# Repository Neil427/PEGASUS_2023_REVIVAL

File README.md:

# PEGASUS_2023_REVIVAL
:

NOTE: FROM 2025 ON DEVELOPMENT WILL CONTINUE ON MY DEDICATED VINTAGE COMPUTER GITHUB "NeilsVintageComputers"

:

This is a reproduction of the first computer I owned back in 1981
After many years and house moves I now dont know whatever happened to it, it may have been sold or dumped, I have no idea.

One day while sorting through floppy disk backups I found all the Pegasus eprom files I had saved dated 1988, including some extra monitor eproms I had made that I think one was for Baudot printer output and the other was for a modification I had made fitting a 6845 CRT controller.
The discovery of the Eprom files and manual with schematics gave me the idea of building a replica, I mentioned this to a mate Gavin who told me he had a unused blank Pegasus circuit board that I could have and build up.  I decided not to build up the board as a bare board is probably quite rare, and without components on it was a great help in verifying the original schematic and designing this new pcb.

Searching found a huge repository on github of Aamber Pegasus software and information (github/Neoncluster/Aamber-Pegasus-remake), the information is a great recource and thanks to Neoncluster for preserving it. 

It looked like this remake was not completed so I decided to start from scratch from the original Pegasus schematics.
I drew the original schematics from the Pegasus manual into Kicad (thanks to Neoncluster for your Kicad Library), finding a few errors in the original documentation which I could verify on the blank PCB. Then started a new Kicad project for the new PCB, I added in the video jitter mods that were done to correct problems with the original Pegasus video design one of which was designed by Gavin back in the 80s.   NOTE: These jitter mds require the use of MON23a monitor eprom.

I have added a 16K Eprom to the board so as to be able to have the three Xbasic eproms on board without needing an expansion board like I used back in 1981, there is also a switch to select two halves of a 32K eprom giving the equivalent of 8 original 4K eproms. 
Also added are option jumpers for the three TMS2532 eprom sockets to allow selection of either TMS2532 or TMS2732 eproms as the TMS2532 is not easy to find these days, and a LED for tape data indication. 

All ICs used are the original ones as in the original pegasus bom, the 74LS logic chips are still available and most of the rareish chips were available on Ebay and other places. The only expensive (read very rare) one was the MCM66710 character generator which I found on Ebay only.

Amazingly it worked first time! All the hours of tracing out what I thought were errors in the original schematic had paid off. 
There was one minor problem I found, if you have no memory/eprom expansion board plugged in but have the LS245 buffer fitted the firmware can read in random data from the expansion bus when doing its check of RamEnd. This causes Basic (or any other program using RamEnd) to crash when trying to use non-existing memory. By luck after trying a few brands (inclding 74HCT245s) I discovered that a Ti brand SN74LS245N worked (Maybe that brand was used in the original Pegasus as I dont remember this being a problem back in 1981), the memory check now doesnt find non-existant memory on the expansion bus. Some pullup resistors on the expansion bus side of these buffers would be a good idea.

Now I had a working Pegasus all I needed was a keyboard. The manual doesnt have the keyboard schematic so this was a lot of work systematically producing key closures and seeing what character they produced!  The first pcb mostly worked, a few of the non printing keys were wrong, so it took another board to correct these. I havent found any errors yet with the current board.  You cant buy cheap Chinese keycaps exactly the same as the old Pegasus keyboard so I have found a set with logical alternatives (i.e."END" for the Break key etc.), you could of course print some stickers with the correct name.
The keyboard has a 34-pin IDC connector as I am going to use it with another board I am working on. For use on the Pegasus main board the "even" side of the idc connector (pins 2-----32) plug into the SIL connector on the main board, alternatively a 16-pin SIL header can be inserted in keyboard pcb connector positions 2-----32 to allow use of SIL connectors as in the original Pegasus (Though my sketchy memory is telling me the KB end of the cable might have been soldered direct to the pcb).  
There are two unused LEDs on the Keyboard pcb intended for use as Power On and Cassette Data, these appear on the 34-pin connector but are not brought out on the main board.

NOTES/ISSUES:
- The resistor on the rear of the pcb is a pullup on the bit7 input to the video output shift register (not in the original Pegasus design) to try and remove a small video disturbance at the top of the screen before the first video character line when in graphics mode. It definalely helped but there is still a small disturbance. Need to look into this further.
Further investigation found a faulty 6809 driving one or two of the address lines to only about 2.5V
Needs further investigation and maybe a "improved" design board to be produced as it looks like the original Pegasus design has many more than 4 LS-TTL loads, as specified in the 6809 datasheet, on the address and data lines. It did still work ok with six out of seven 6809 chips I tried. Just one didnt work 100% reliably.
- The 127p capacitor C10 on the dotclock oscillator can be adjusted to trim the dotclock frequency. I noticed on my build that the shift register was clocking out a extra bit making the characters wider than they should be, not really noticeable in text mode but in inverse char graphics mode there would be a "lit up" column of dots at the right of each character.  If the dotclock is too slow the oposite will happen which is noticeable in both text and graphics mode as trimming of the right most dot of a character. I ended up with 138pF (120p + 18p).
- The PCB although the same dimension as the original cant be slid into the original Pegasus square white case as I inadvertently laid the power tracks too close to the edge of the pcb!
- The resistor footprint used is a bit large, needs reducing if producing a update to the board.
  
Here are some phtos of the finished "Pegasus"

Neil

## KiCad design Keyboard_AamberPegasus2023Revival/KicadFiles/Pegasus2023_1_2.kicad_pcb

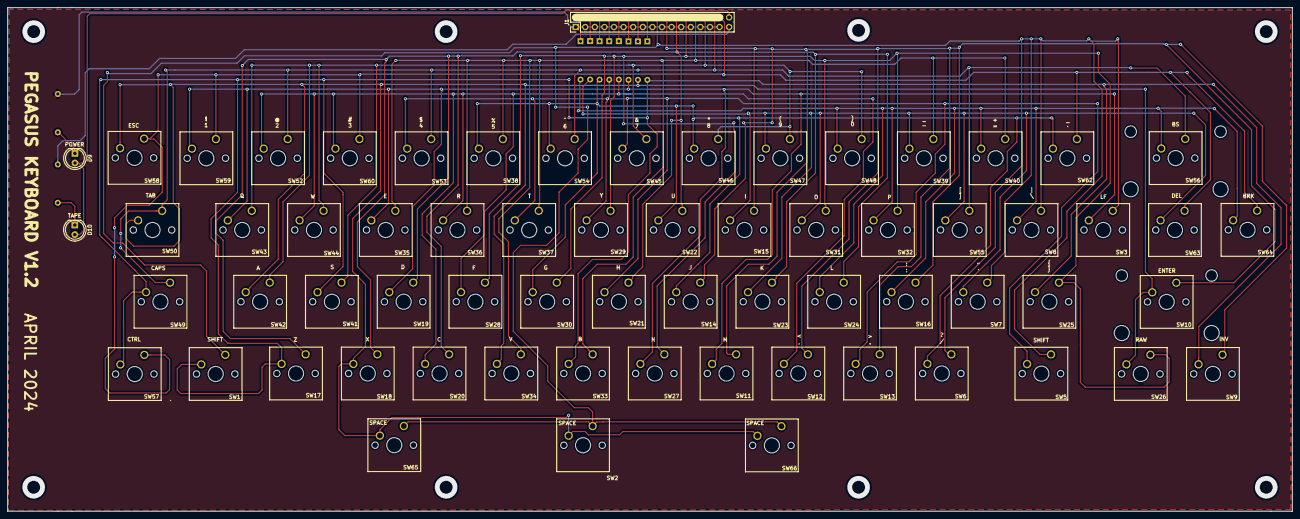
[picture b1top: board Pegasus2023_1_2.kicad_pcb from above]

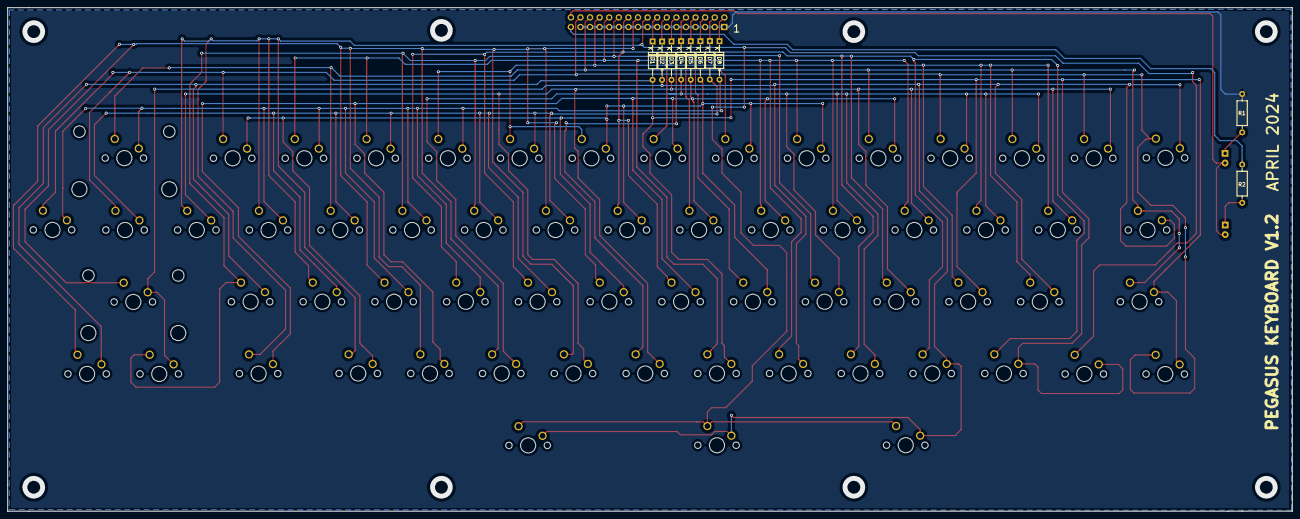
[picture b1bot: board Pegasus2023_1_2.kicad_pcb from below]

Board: 2 copper layers, 340.2 x 133.4 mm, 76 parts (10 on the bottom side), 29 nets.

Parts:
D1, D2, D3, D4, D5, D6, D7, D8: BAT42; D_DO-35_SOD27_P10.16mm_Horizontal
D9: POWER LED; LED_D5.0mm
D10: TAPE LED; LED_D5.0mm
J1: Conn_02x17_Odd_Even; PinHeader_2x17_P2.54mm_Vertical
R1, R2: 470R; R_Axial_DIN0207_L6.3mm_D2.5mm_P10.16mm_Horizontal
SW1: LH SHIFT; SW_Cherry_MX_1.75u_PCB
SW2: SPACE; SW_Cherry_MX_1.00u_PCB
SW3: LF; SW_Cherry_MX_1.00u_PCB
SW5: RH SHIFT; SW_Cherry_MX_1.75u_PCB
SW6: / & ?; SW_Cherry_MX_1.00u_PCB
SW7: ' & "; SW_Cherry_MX_1.00u_PCB
SW8: \ & |; SW_Cherry_MX_1.00u_PCB
SW9: INV; SW_Cherry_MX_1.00u_PCB
SW10: RETURN; SW_Cherry_MX_2.25u_PCB
SW11: M; SW_Cherry_MX_1.00u_PCB
SW12: <; SW_Cherry_MX_1.00u_PCB
SW13: >; SW_Cherry_MX_1.00u_PCB
SW14: J; SW_Cherry_MX_1.00u_PCB
SW15: I; SW_Cherry_MX_1.00u_PCB
SW16: ; & :; SW_Cherry_MX_1.00u_PCB
SW17: Z; SW_Cherry_MX_1.00u_PCB
SW18: X; SW_Cherry_MX_1.00u_PCB
SW19: D; SW_Cherry_MX_1.00u_PCB
SW20: C; SW_Cherry_MX_1.00u_PCB
SW21: H; SW_Cherry_MX_1.00u_PCB
SW22: U; SW_Cherry_MX_1.00u_PCB
SW23: K; SW_Cherry_MX_1.00u_PCB
SW24: L; SW_Cherry_MX_1.00u_PCB
SW25: { & }; SW_Cherry_MX_1.00u_PCB
SW26: RAW; SW_Cherry_MX_1.00u_PCB
SW27: N; SW_Cherry_MX_1.00u_PCB
SW28: F; SW_Cherry_MX_1.00u_PCB
SW29: Y; SW_Cherry_MX_1.00u_PCB
SW30: G; SW_Cherry_MX_1.00u_PCB
SW31: O; SW_Cherry_MX_1.00u_PCB
SW32: P; SW_Cherry_MX_1.00u_PCB
SW33: B; SW_Cherry_MX_1.00u_PCB
SW34: V; SW_Cherry_MX_1.00u_PCB
SW35: E; SW_Cherry_MX_1.00u_PCB
SW36: R; SW_Cherry_MX_1.00u_PCB
SW37: T; SW_Cherry_MX_1.00u_PCB
SW38: 5 & %; SW_Cherry_MX_1.00u_PCB
SW39: - & _; SW_Cherry_MX_1.00u_PCB
SW40: = & +; SW_Cherry_MX_1.00u_PCB
SW41: S; SW_Cherry_MX_1.00u_PCB
SW42: A; SW_Cherry_MX_1.00u_PCB
SW43: Q; SW_Cherry_MX_1.00u_PCB
SW44: W; SW_Cherry_MX_1.00u_PCB
SW45: 7 & &; SW_Cherry_MX_1.00u_PCB
SW46: 8 & *; SW_Cherry_MX_1.00u_PCB
SW47: 9 & (; SW_Cherry_MX_1.00u_PCB
SW48: 0 & ); SW_Cherry_MX_1.00u_PCB
SW49: CAPS; SW_Cherry_MX_1.25u_PCB
SW50: TAB; SW_Cherry_MX_1.50u_PCB
SW52: 2 & @; SW_Cherry_MX_1.00u_PCB
SW53: 4 & $; SW_Cherry_MX_1.00u_PCB
SW54: 6 & ^; SW_Cherry_MX_1.00u_PCB
SW55: ] & [; SW_Cherry_MX_1.00u_PCB
SW56: BS; SW_Cherry_MX_2.00u_PCB
SW57: CTRL; SW_Cherry_MX_1.00u_PCB
SW58: ESC; SW_Cherry_MX_1.00u_PCB
SW59: 1 & !; SW_Cherry_MX_1.00u_PCB
SW60: 3 & #; SW_Cherry_MX_1.00u_PCB
SW62: ~ & `; SW_Cherry_MX_1.00u_PCB
SW63: DEL; SW_Cherry_MX_1.00u_PCB
SW64: BRK; SW_Cherry_MX_1.00u_PCB
SW65: Lspace; SW_Cherry_MX_1.00u_PCB
SW66: Rspace; SW_Cherry_MX_1.00u_PCB

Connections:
7-9: D2.2, SW2.2, SW10.2, SW18.2, SW26.2, SW34.2, SW42.2, SW50.2, SW58.2, SW65.2, SW66.2
+5V: D9.2, D10.2, J1.34
GND: J1.1, J1.3, J1.5, J1.7, J1.9, J1.11, J1.13, J1.15, J1.17, J1.19, J1.21, J1.23, J1.25, J1.27, J1.29, J1.31, R1.1
unnamed: D1.1, J1.16
unnamed: D1.2, SW1.2, SW9.2, SW17.2, SW25.2, SW33.2, SW41.2, SW49.2, SW57.2
unnamed: D2.1, J1.14
unnamed: D3.1, J1.12
unnamed: D3.2, SW3.2, SW11.2, SW19.2, SW27.2, SW35.2, SW43.2, SW59.2
unnamed: D4.1, J1.10
unnamed: D4.2, SW12.2, SW20.2, SW28.2, SW36.2, SW44.2, SW52.2, SW60.2
unnamed: D5.1, J1.8
unnamed: D5.2, SW5.2, SW13.2, SW21.2, SW29.2, SW37.2, SW45.2, SW53.2
unnamed: D6.1, J1.6
unnamed: D6.2, SW6.2, SW14.2, SW22.2, SW30.2, SW38.2, SW46.2, SW54.2, SW62.2
unnamed: D7.1, J1.4
unnamed: D7.2, SW7.2, SW15.2, SW23.2, SW31.2, SW39.2, SW47.2, SW55.2, SW63.2
unnamed: D8.1, J1.2
unnamed: D8.2, SW8.2, SW16.2, SW24.2, SW32.2, SW40.2, SW48.2, SW56.2, SW64.2
unnamed: D9.1, R1.2
unnamed: D10.1, R2.2
unnamed: J1.18, SW1.1, SW2.1, SW3.1, SW5.1, SW6.1, SW7.1, SW8.1, SW65.1, SW66.1
unnamed: J1.20, SW9.1, SW10.1, SW11.1, SW12.1, SW13.1, SW14.1, SW15.1, SW16.1
unnamed: J1.22, SW17.1, SW18.1, SW19.1, SW20.1, SW21.1, SW22.1, SW23.1, SW24.1
unnamed: J1.24, SW25.1, SW26.1, SW27.1, SW28.1, SW29.1, SW30.1, SW31.1, SW32.1
unnamed: J1.26, SW33.1, SW34.1, SW35.1, SW36.1, SW37.1, SW38.1, SW39.1, SW40.1
unnamed: J1.28, SW41.1, SW42.1, SW43.1, SW44.1, SW45.1, SW46.1, SW47.1, SW48.1
unnamed: J1.30, SW49.1, SW50.1, SW52.1, SW53.1, SW54.1, SW55.1, SW56.1
unnamed: J1.32, SW57.1, SW58.1, SW59.1, SW60.1, SW62.1, SW63.1, SW64.1
unnamed: J1.33, R2.1

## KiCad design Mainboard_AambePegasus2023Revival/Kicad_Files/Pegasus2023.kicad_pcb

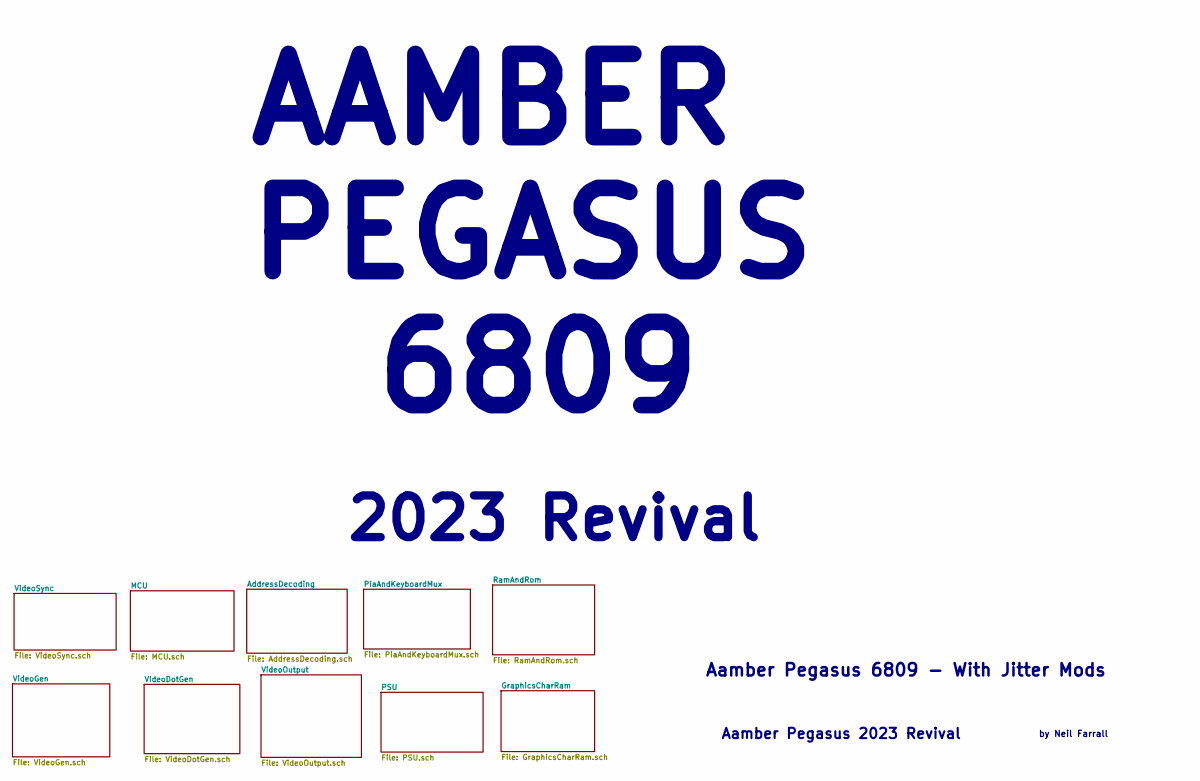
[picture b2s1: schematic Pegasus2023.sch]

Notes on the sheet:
Aamber Pegasus 2023 Revival
by Neil Farrall
Aamber Pegasus 6809 - With Jitter Mods
AAMBER PEGASUS 6809
2023 Revival

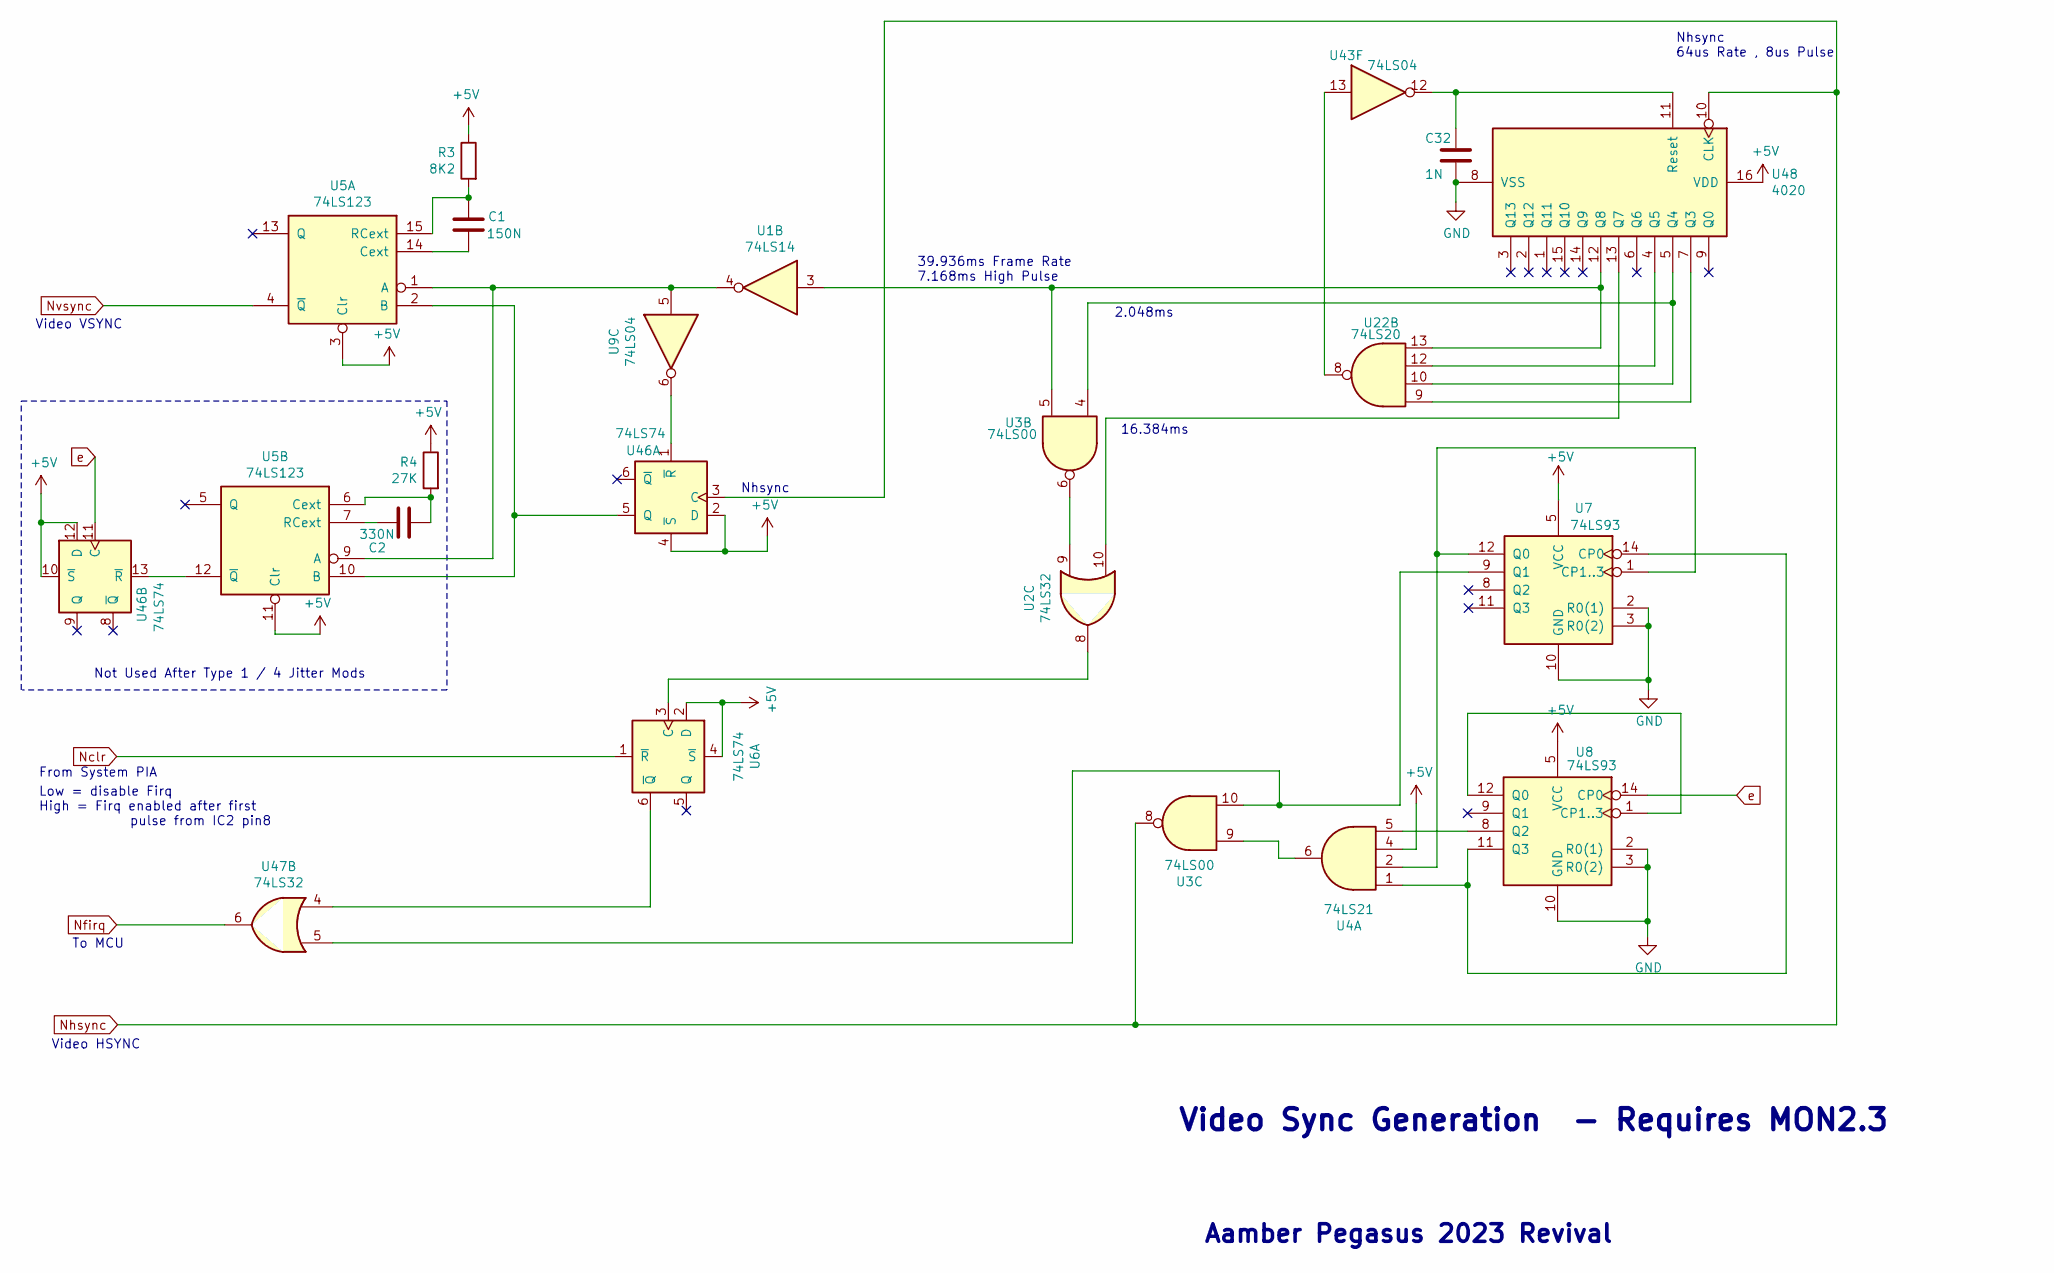
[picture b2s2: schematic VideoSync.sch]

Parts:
C1: 150N; C_Rect_L7.5mm_W6.5mm_P5.00mm
C2: 330N; C_Rect_L7.5mm_W6.5mm_P5.00mm
C32: 1N; C_Disc_D4.3mm_W1.9mm_P5.00mm
R3: 8K2; R_Axial_DIN0411_L9.9mm_D3.6mm_P15.24mm_Horizontal
R4: 27K; R_Axial_DIN0411_L9.9mm_D3.6mm_P15.24mm_Horizontal
U1: 74LS14; DIP-14_W7.62mm_Socket_LongPads
U2, U47: 74LS32; DIP-14_W7.62mm_Socket_LongPads
U3: 74LS00; DIP-14_W7.62mm_Socket_LongPads
U4: 74LS21; DIP-14_W7.62mm_Socket_LongPads
U5: 74LS123; DIP-16_W7.62mm_Socket_LongPads
U6, U46: 74LS74; DIP-14_W7.62mm_Socket_LongPads
U7, U8: 74LS93; DIP-14_W7.62mm_Socket_LongPads
U9, U43: 74LS04; DIP-14_W7.62mm_Socket_LongPads
U22: 74LS20; DIP-14_W7.62mm_Socket_LongPads
U48: 4020; DIP-16_W7.62mm_Socket_LongPads

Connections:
Nclr: U6.1 (~R); also elsewhere on the board
unnamed: C1.1, R3.2, U5.15 (RCext)
unnamed: C1.2, U5.14 (Cext)
unnamed: C2.1, R4.2, U5.6 (Cext)
unnamed: C2.2, U5.7 (RCext)
unnamed: C32.1, U43.12, U48.11 (Reset)
unnamed: U1.3, U3.5, U22.13, U48.12 (Q8)
unnamed: U1.4, U5.1 (A), U5.9 (A), U9.5
unnamed: U2.8, U6.3 (C)
unnamed: U2.9, U3.6
unnamed: U2.10, U48.13 (Q7)
unnamed: U3.9, U4.6
unnamed: U3.10, U7.9 (Q1), U47.5
unnamed: U4.1, U7.14 (CP0), U8.11 (Q3)
unnamed: U4.2, U7.1 (CP1..3), U7.12 (Q0)
unnamed: U4.5, U8.8 (Q2)
unnamed: U8.1 (CP1..3), U8.12 (Q0)
unnamed: U22.8, U43.13
unnamed: U22.9, U48.7 (Q3)
unnamed: U3.4, U22.10, U48.5 (Q4)
unnamed: U22.12, U48.4 (Q5)
unnamed: U9.6, U46.1 (~R)
unnamed: U5.2 (B), U5.10 (B), U46.5 (Q)
unnamed: U5.12 (~Q), U46.13 (~R)
unnamed: U6.6 (~Q), U47.4
Nfirq: U47.6; also elsewhere on the board
Nhsync: U3.8, U46.3 (C), U48.10 (CLK); also elsewhere on the board
Nvsync: U5.4 (~Q); also elsewhere on the board
e: U8.14 (CP0), U46.11 (C); also elsewhere on the board

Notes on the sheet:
Aamber Pegasus 2023 Revival
Video Sync Generation - Requires MON2.3
From System PIA
To MCU
Video HSYNC
Video VSYNC
Not Used After Type 1 / 4 Jitter Mods
Nhsync
Nhsync 64us Rate , 8us Pulse
Low = disable Firq High = Firq enabled after first pulse from IC2 pin8
39.936ms Frame Rate 7.168ms High Pulse
2.048ms
16.384ms

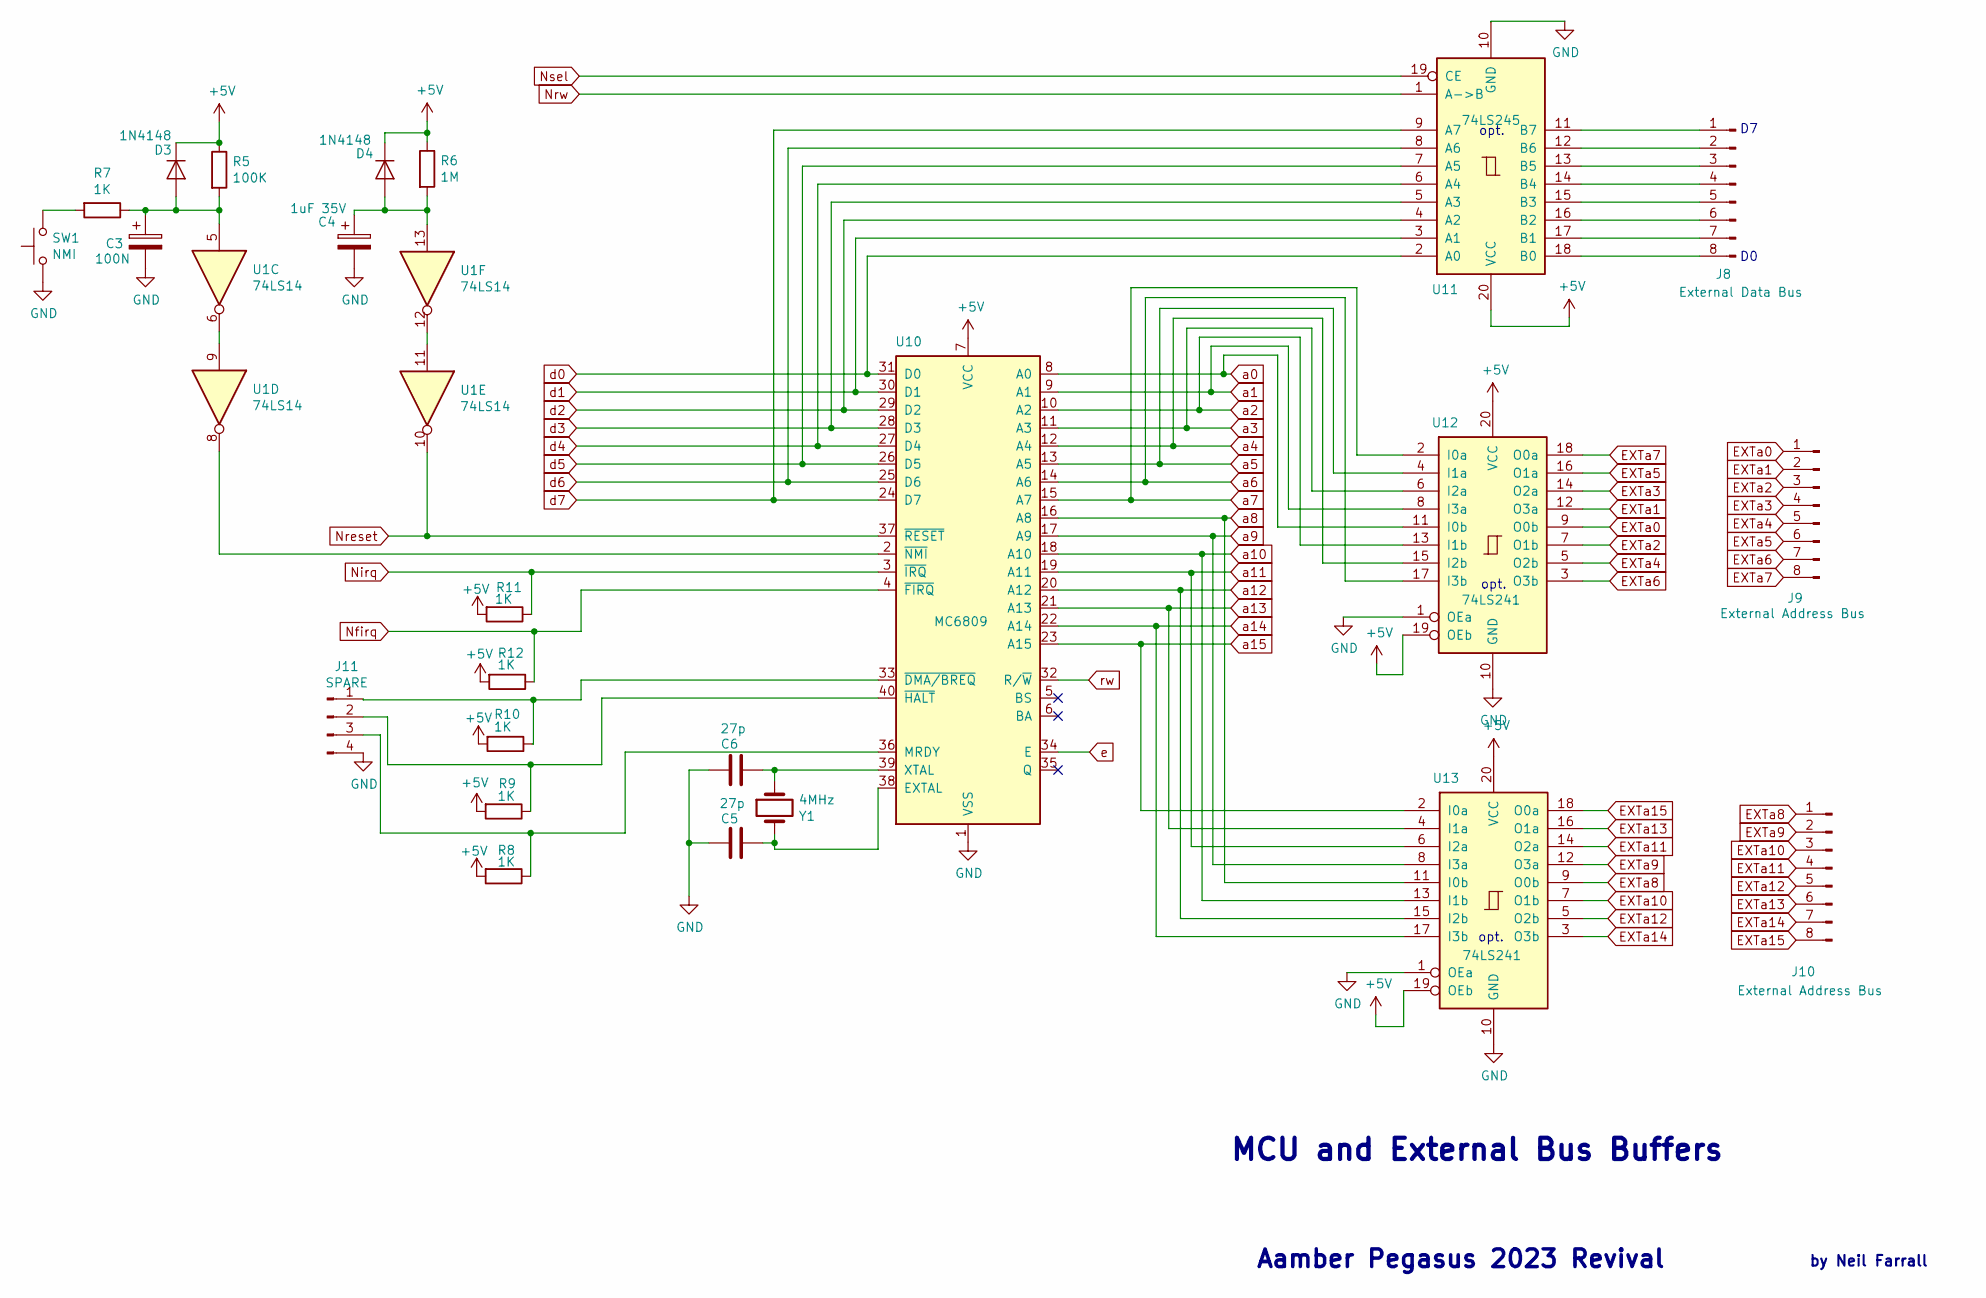
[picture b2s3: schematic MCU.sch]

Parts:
C3: 100N; C_Disc_D11.0mm_W5.0mm_P5.00mm
C4: 1uF 35V; CP_Radial_D5.0mm_P2.50mm
C5, C6: 27p; C_Disc_D3.8mm_W2.6mm_P2.50mm
D3, D4: 1N4148; D_DO-15_P12.70mm_Horizontal
J8: External Data Bus; PinHeader_1x08_P2.54mm_Horizontal
J9, J10: External Address Bus; PinHeader_1x08_P2.54mm_Horizontal
J11: SPARE; PinHeader_1x04_P2.54mm_Vertical
R5: 100K; R_Axial_DIN0411_L9.9mm_D3.6mm_P15.24mm_Horizontal
R6: 1M; R_Axial_DIN0411_L9.9mm_D3.6mm_P15.24mm_Horizontal
R7, R8, R9, R10, R11, R12: 1K; R_Axial_DIN0411_L9.9mm_D3.6mm_P15.24mm_Horizontal
SW1: NMI; SW_PUSH_6mm_H5mm
U1: 74LS14; DIP-14_W7.62mm_Socket_LongPads
U10: MC6809; DIP-40_W15.24mm_Socket_LongPads
U11: 74LS245; DIP-20_W7.62mm_Socket_LongPads
U12, U13: 74LS241; DIP-20_W7.62mm_Socket_LongPads
Y1: 4MHz; Crystal_HC49-U_Horizontal_1EP_style2

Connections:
EXTa0: J9.1, U12.9 (O0b)
EXTa1: J9.2, U12.12 (O3a)
EXTa2: J9.3, U12.7 (O1b)
EXTa3: J9.4, U12.14 (O2a)
EXTa4: J9.5, U12.5 (O2b)
EXTa5: J9.6, U12.16 (O1a)
EXTa6: J9.7, U12.3 (O3b)
EXTa7: J9.8, U12.18 (O0a)
EXTa8: J10.1, U13.9 (O0b)
EXTa9: J10.2, U13.12 (O3a)
EXTa10: J10.3, U13.7 (O1b)
EXTa11: J10.4, U13.14 (O2a)
EXTa12: J10.5, U13.5 (O2b)
EXTa13: J10.6, U13.16 (O1a)
EXTa14: J10.7, U13.3 (O3b)
EXTa15: J10.8, U13.18 (O0a)
unnamed: C3.1, D3.2 (A), R5.2, R7.1, U1.5
unnamed: C4.1, D4.2 (A), R6.2, U1.13
unnamed: C5.1, U10.38 (EXTAL), Y1.2
unnamed: C6.1, U10.39 (XTAL), Y1.1
unnamed: J8.1, U11.11 (B7)
unnamed: J8.2, U11.12 (B6)
unnamed: J8.3, U11.13 (B5)
unnamed: J8.4, U11.14 (B4)
unnamed: J8.5, U11.15 (B3)
unnamed: J8.6, U11.16 (B2)
unnamed: J8.7, U11.17 (B1)
unnamed: J8.8, U11.18 (B0)
unnamed: J11.1, R10.1, U10.33 (~DMA/BREQ)
unnamed: J11.2, R9.1, U10.40 (~HALT)
unnamed: J11.3, R8.1, U10.36 (MRDY)
unnamed: R7.2, SW1.2
unnamed: U1.6, U1.9
unnamed: U1.8, U10.2 (~NMI)
unnamed: U1.11, U1.12
Nfirq: R12.1, U10.4 (~FIRQ); also elsewhere on the board
Nirq: R11.1, U10.3 (~IRQ); also elsewhere on the board
Nreset: U1.10, U10.37 (~RESET); also elsewhere on the board
Nrw: U11.1 (A->B); also elsewhere on the board
Nsel: U11.19 (CE); also elsewhere on the board
a0: U10.8 (A0), U12.11 (I0b); also elsewhere on the board
a1: U10.9 (A1), U12.8 (I3a); also elsewhere on the board
a2: U10.10 (A2), U12.13 (I1b); also elsewhere on the board
a3: U10.11 (A3), U12.6 (I2a); also elsewhere on the board
a4: U10.12 (A4), U12.15 (I2b); also elsewhere on the board
a5: U10.13 (A5), U12.4 (I1a); also elsewhere on the board
a6: U10.14 (A6), U12.17 (I3b); also elsewhere on the board
a7: U10.15 (A7), U12.2 (I0a); also elsewhere on the board
a8: U10.16 (A8), U13.11 (I0b); also elsewhere on the board
a9: U10.17 (A9), U13.8 (I3a); also elsewhere on the board
a10: U10.18 (A10), U13.13 (I1b); also elsewhere on the board
a11: U10.19 (A11), U13.6 (I2a); also elsewhere on the board
a12: U10.20 (A12), U13.15 (I2b); also elsewhere on the board
a13: U10.21 (A13), U13.4 (I1a); also elsewhere on the board
a14: U10.22 (A14), U13.17 (I3b); also elsewhere on the board
a15: U10.23 (A15), U13.2 (I0a); also elsewhere on the board
d0: U10.31 (D0), U11.2 (A0); also elsewhere on the board
d1: U10.30 (D1), U11.3 (A1); also elsewhere on the board
d2: U10.29 (D2), U11.4 (A2); also elsewhere on the board
d3: U10.28 (D3), U11.5 (A3); also elsewhere on the board
d4: U10.27 (D4), U11.6 (A4); also elsewhere on the board
d5: U10.26 (D5), U11.7 (A5); also elsewhere on the board
d6: U10.25 (D6), U11.8 (A6); also elsewhere on the board
d7: U10.24 (D7), U11.9 (A7); also elsewhere on the board
e: U10.34 (E); also elsewhere on the board
rw: U10.32 (R/~W); also elsewhere on the board

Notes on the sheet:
opt.
MCU and External Bus Buffers
Aamber Pegasus 2023 Revival
by Neil Farrall

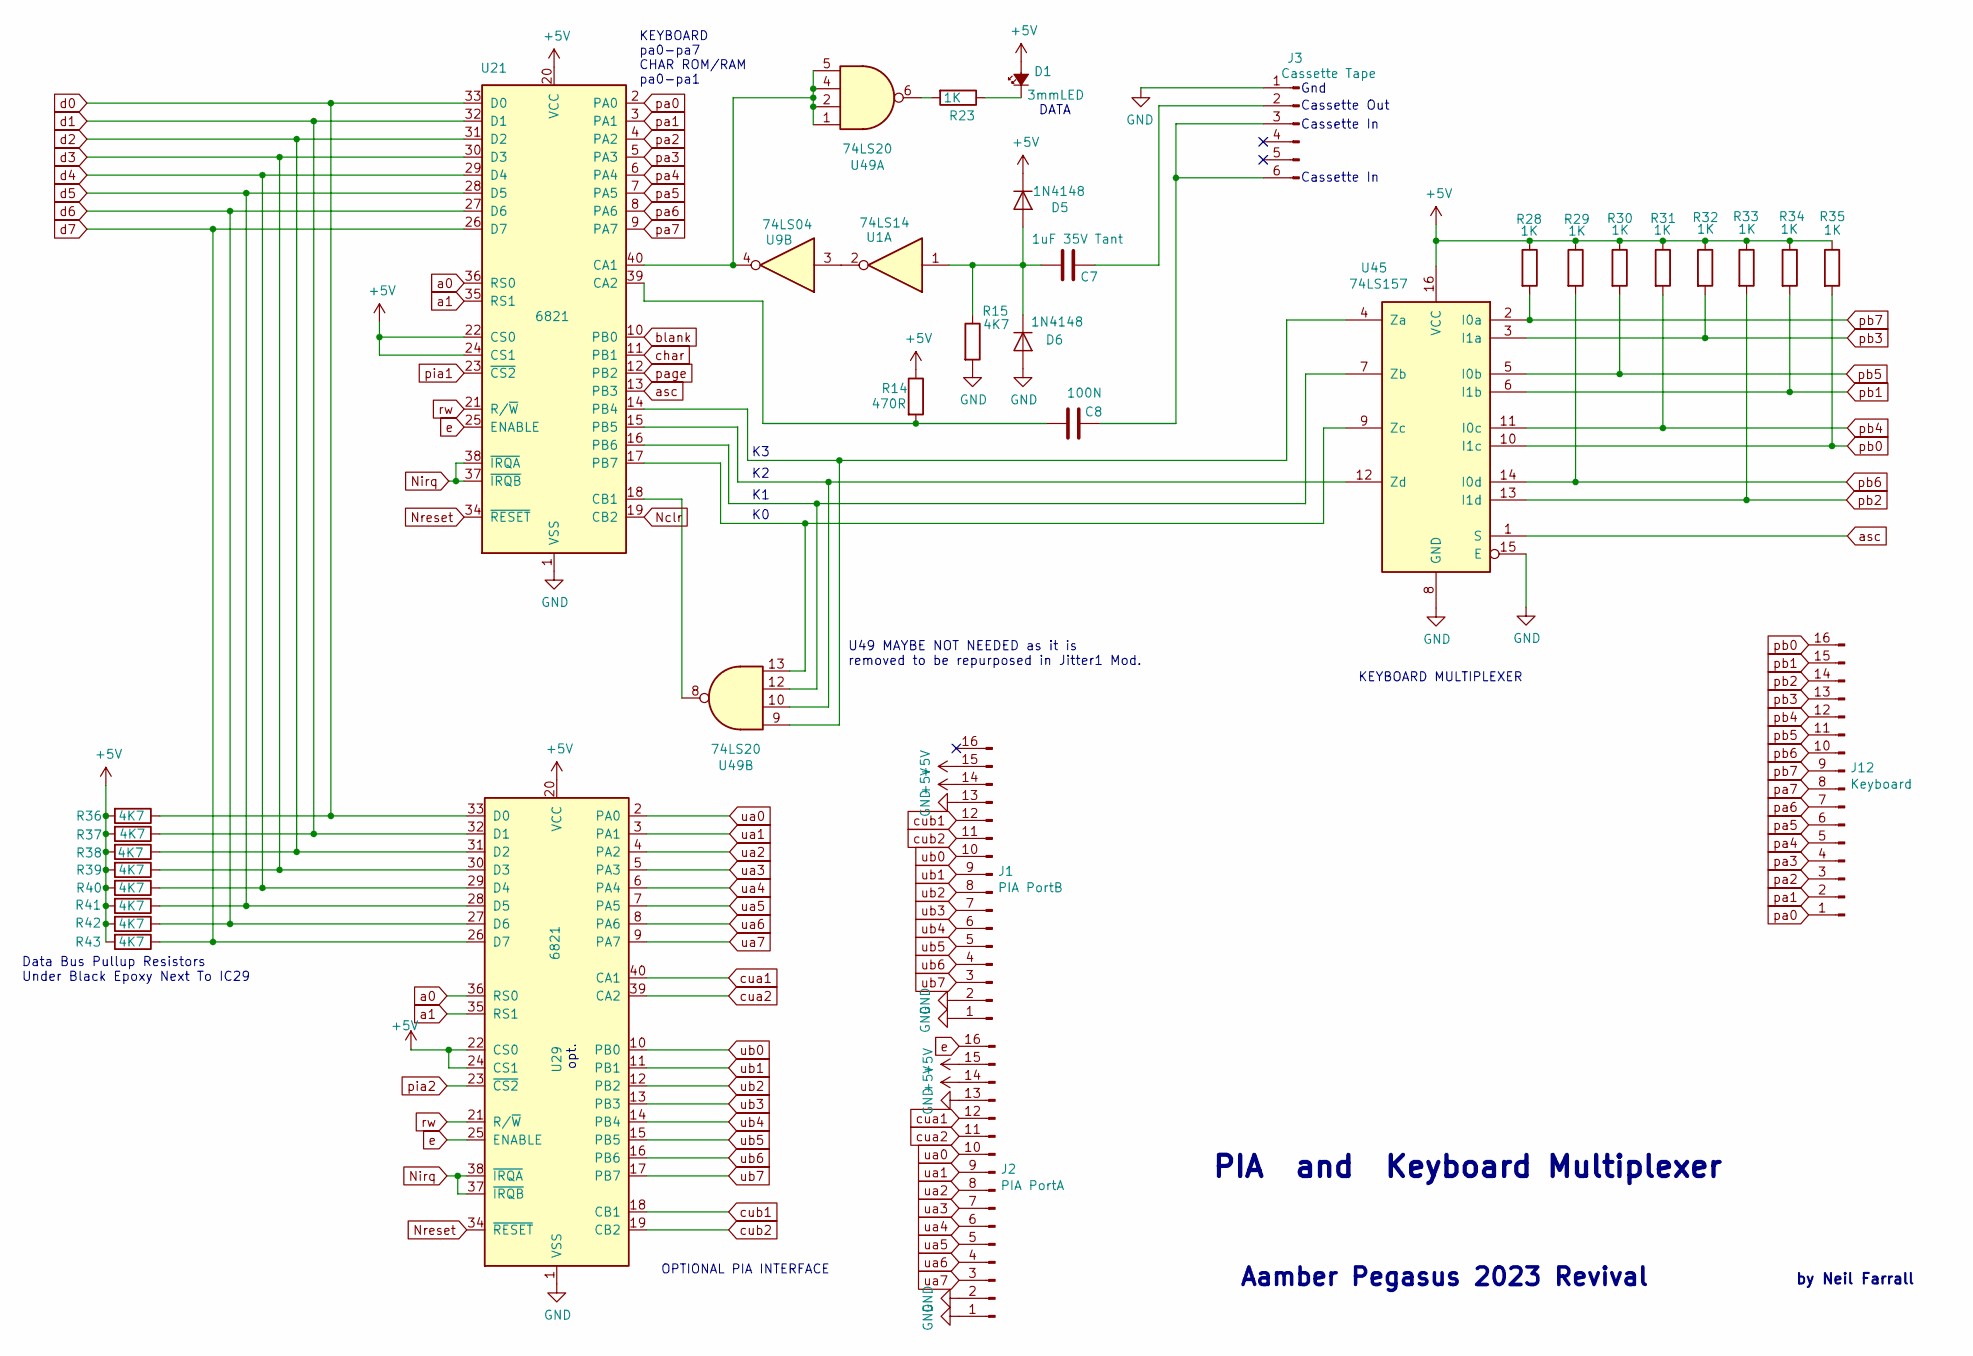
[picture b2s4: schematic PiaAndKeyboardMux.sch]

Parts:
C7: 1uF 35V Tant; CP_Radial_Tantal_D5.0mm_P2.50mm
C8: 100N; C_Disc_D11.0mm_W5.0mm_P5.00mm
D1: 3mmLED; LED_D5.0mm
D5, D6: 1N4148; D_DO-15_P12.70mm_Horizontal
J1: PIA PortB; PinHeader_1x16_P2.54mm_Horizontal
J2: PIA PortA; PinHeader_1x16_P2.54mm_Horizontal
J3: Cassette Tape; PinHeader_1x06_P2.54mm_Horizontal
J12: Keyboard; PinHeader_1x16_P2.54mm_Horizontal
R14: 470R; R_Axial_DIN0411_L9.9mm_D3.6mm_P15.24mm_Horizontal
R15, R36, R37, R38, R39, R40, R41, R42, R43: 4K7; R_Axial_DIN0411_L9.9mm_D3.6mm_P15.24mm_Horizontal
R23, R28, R29, R30, R31, R32, R33, R34, R35: 1K; R_Axial_DIN0411_L9.9mm_D3.6mm_P15.24mm_Horizontal
U1: 74LS14; DIP-14_W7.62mm_Socket_LongPads
U9: 74LS04; DIP-14_W7.62mm_Socket_LongPads
U21, U29: 6821; DIP-40_W15.24mm_Socket_LongPads
U45: 74LS157; DIP-16_W7.62mm_Socket_LongPads
U49: 74LS20; DIP-14_W7.62mm_Socket_LongPads

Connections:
Nclr: U21.19 (CB2); also elsewhere on the board
unnamed: C7.1, J3.2
unnamed: C7.2, D5.2 (A), D6.1 (K), R15.1, U1.1
unnamed: C8.1, J3.3, J3.6
unnamed: C8.2, R14.2, U21.39 (CA2)
unnamed: D1.1 (K), R23.1
unnamed: R23.2, U49.6
unnamed: U1.2, U9.3
unnamed: U21.14 (PB4), U45.4 (Za), U49.9
unnamed: U21.15 (PB5), U45.12 (Zd), U49.10
unnamed: U21.16 (PB6), U45.7 (Zb), U49.12
unnamed: U21.17 (PB7), U45.9 (Zc), U49.13
unnamed: U21.18 (CB1), U49.8
unnamed: U9.4, U21.40 (CA1), U49.1, U49.2, U49.4, U49.5
Nirq: U21.37 (~IRQB), U21.38 (~IRQA), U29.37 (~IRQB), U29.38 (~IRQA); also elsewhere on the board
Nreset: U21.34 (~RESET), U29.34 (~RESET); also elsewhere on the board
a0: U21.36 (RS0), U29.36 (RS0); also elsewhere on the board
a1: U21.35 (RS1), U29.35 (RS1); also elsewhere on the board
asc: U21.13 (PB3), U45.1 (S)
blank: U21.10 (PB0); also elsewhere on the board
char: U21.11 (PB1); also elsewhere on the board
cua1: J2.12, U29.40 (CA1)
cua2: J2.11, U29.39 (CA2)
cub1: J1.12, U29.18 (CB1)
cub2: J1.11, U29.19 (CB2)
d0: R36.1, U21.33 (D0), U29.33 (D0); also elsewhere on the board
d1: R37.1, U21.32 (D1), U29.32 (D1); also elsewhere on the board
d2: R38.1, U21.31 (D2), U29.31 (D2); also elsewhere on the board
d3: R39.1, U21.30 (D3), U29.30 (D3); also elsewhere on the board
d4: R40.1, U21.29 (D4), U29.29 (D4); also elsewhere on the board
d5: R41.1, U21.28 (D5), U29.28 (D5); also elsewhere on the board
d6: R42.1, U21.27 (D6), U29.27 (D6); also elsewhere on the board
d7: R43.1, U21.26 (D7), U29.26 (D7); also elsewhere on the board
e: J2.16, U21.25 (ENABLE), U29.25 (ENABLE); also elsewhere on the board
pa0: J12.1, U21.2 (PA0); also elsewhere on the board
pa1: J12.2, U21.3 (PA1); also elsewhere on the board
pa2: J12.3, U21.4 (PA2); also elsewhere on the board
pa3: J12.4, U21.5 (PA3); also elsewhere on the board
pa4: J12.5, U21.6 (PA4)
pa5: J12.6, U21.7 (PA5)
pa6: J12.7, U21.8 (PA6)
pa7: J12.8, U21.9 (PA7)
page: U21.12 (PB2); also elsewhere on the board
pb0: J12.16, R35.2, U45.10 (I1c)
pb1: J12.15, R34.2, U45.6 (I1b)
pb2: J12.14, R33.2, U45.13 (I1d)
pb3: J12.13, R32.2, U45.3 (I1a)
pb4: J12.12, R31.2, U45.11 (I0c)
pb5: J12.11, R30.2, U45.5 (I0b)
pb6: J12.10, R29.2, U45.14 (I0d)
pb7: J12.9, R28.2, U45.2 (I0a)
pia1: U21.23 (~CS2); also elsewhere on the board
pia2: U29.23 (~CS2); also elsewhere on the board
rw: U21.21 (R/~W), U29.21 (R/~W); also elsewhere on the board
ua0: J2.10, U29.2 (PA0)
ua1: J2.9, U29.3 (PA1)
ua2: J2.8, U29.4 (PA2)
ua3: J2.7, U29.5 (PA3)
ua4: J2.6, U29.6 (PA4)
ua5: J2.5, U29.7 (PA5)
ua6: J2.4, U29.8 (PA6)
ua7: J2.3, U29.9 (PA7)
ub0: J1.10, U29.10 (PB0)
ub1: J1.9, U29.11 (PB1)
ub2: J1.8, U29.12 (PB2)
ub3: J1.7, U29.13 (PB3)
ub4: J1.6, U29.14 (PB4)
ub5: J1.5, U29.15 (PB5)
ub6: J1.4, U29.16 (PB6)
ub7: J1.3, U29.17 (PB7)

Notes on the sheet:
Aamber Pegasus 2023 Revival
by Neil Farrall
PIA and Keyboard Multiplexer
KEYBOARD MULTIPLEXER
OPTIONAL PIA INTERFACE
opt.
U49 MAYBE NOT NEEDED as it is removed to be repurposed in Jitter1 Mod.
Cassette Out
Cassette In
Gnd
Data Bus Pullup Resistors Under Black Epoxy Next To IC29
KEYBOARD pa0-pa7 CHAR ROM/RAM pa0-pa1
DATA
